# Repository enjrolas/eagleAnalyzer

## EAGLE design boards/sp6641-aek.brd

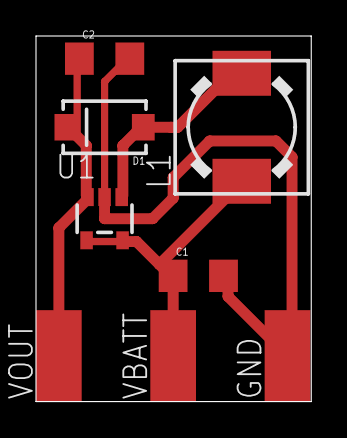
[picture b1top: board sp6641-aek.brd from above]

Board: 2 copper layers, 15.3 x 20.3 mm, 8 parts (0 on the bottom side), 4 nets.

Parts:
C1, C2: 22uF; 1206
D1: DIODE-SCHOTTKY_; SMA-DIODE
GND: SMD2,54-5,08
L1: 22uH; DR73
U1: SP6641AEK; SOT23-5
VBATT: SMD2,54-5,08
VOUT: SMD2,54-5,08

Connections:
GND: C1.2, C2.2, GND.1, U1.2
unnamed: D1.A, L1.2, U1.1
VBATT: C1.1, L1.1, U1.4, U1.5, VBATT.1
VOUT: C2.1, D1.C, U1.3, VOUT.1

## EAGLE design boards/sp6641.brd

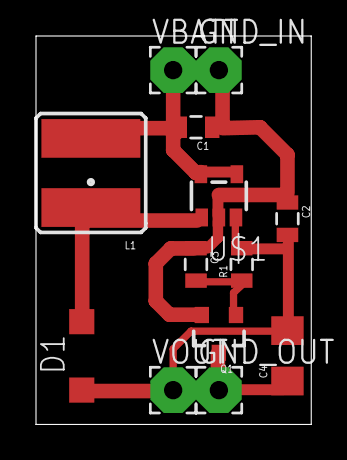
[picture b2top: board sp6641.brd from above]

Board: 2 copper layers, 15.3 x 21.6 mm, 13 parts (0 on the bottom side), 6 nets.

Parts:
C1, C2: 22uF; 0805
C3: 10nF; 0805
C4: 1uF; 1206
D1: MBR0520; SOD123
GND_IN: 2,54/1,0
GND_OUT: 2,54/1,0
L1: 22uH; CR54
Q1: SOT23-3
R1: 2M; 0805
U$1: SP6641A; SOT23-5
VBATT: 2,54/1,0
VOUT: 2,54/1,0

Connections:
GND: C1.1, C2.1, C3.1, GND_IN.1, Q1.2, U$1.2
GND_OUT: C4.1, GND_OUT.1, Q1.3
unnamed: C3.2, Q1.1, R1.1
unnamed: D1.A, L1.P$1, U$1.1
VBATT: C1.2, L1.P$2, U$1.4, U$1.5, VBATT.1
VOUT: C2.2, C4.2, D1.C, R1.2, U$1.3, VOUT.1

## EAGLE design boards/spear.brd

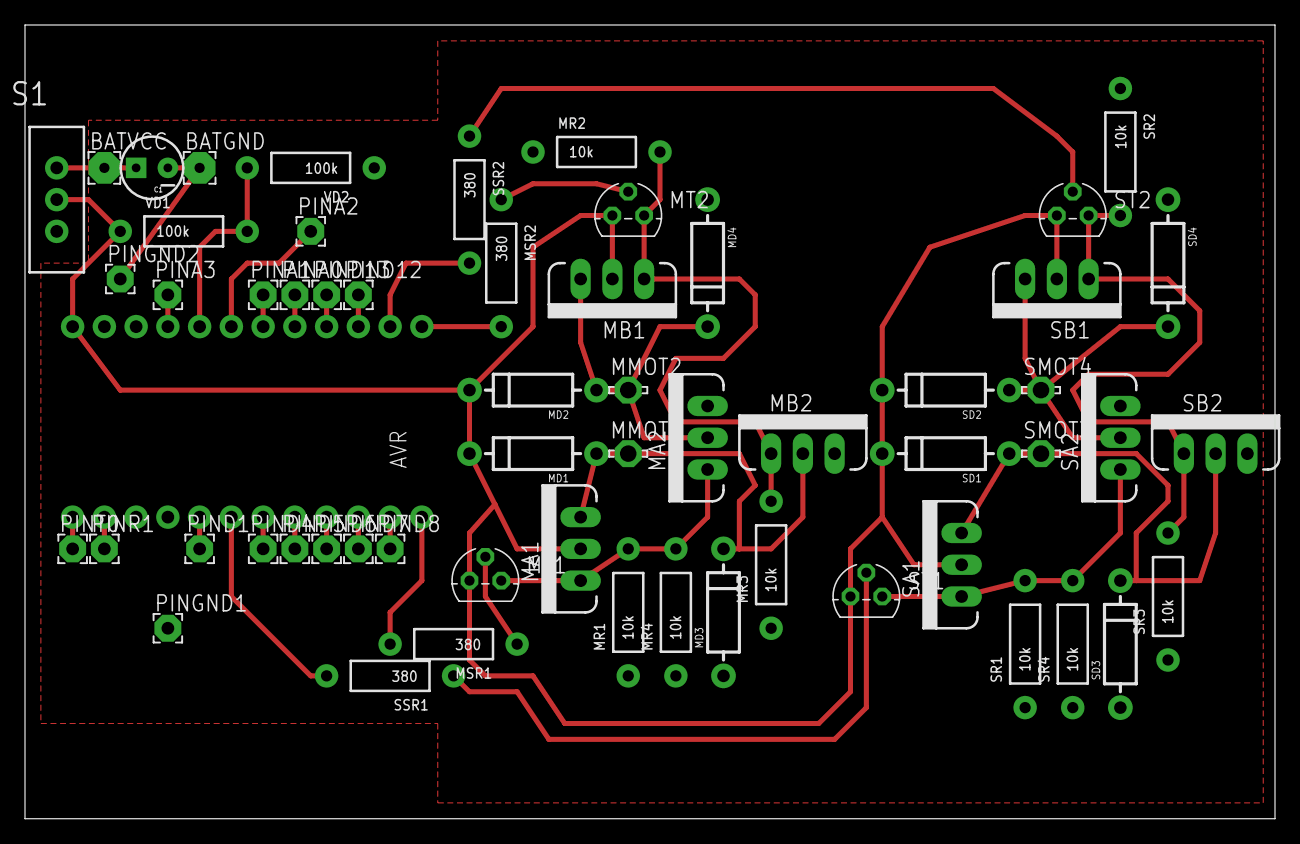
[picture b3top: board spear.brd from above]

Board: 2 copper layers, 100.0 x 63.5 mm, 59 parts (0 on the bottom side), 34 nets.

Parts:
AVR: ARDUINO_MINI
BATGND: WIREPAD2,54/0,8; 2,54/0,8
BATVCC: WIREPAD2,54/0,8; 2,54/0,8
C1: 10uf; CPOL-RADIAL-10UF-25V
MA1, MA2: MOSFET-NCHANNELFQP30N06L; TO220V
MB1, MB2: MOSFET-NCHANNELFQP30N06L; TO220V
MD1, MD2, MD3, MD4: DIODE-1N4001
MMOT1, MMOT2: LSP13
MR1, MR2, MR3, MR4: 10k; AXIAL-0.4
MSR1, MSR2: 380; AXIAL-0.4
MT1, MT2: 2N3904; TO92
PINA0, PINA1, PINA2, PINA3: WIREPAD2,15/1,0; 2,15/1,0
PIND1, PIND4, PIND5, PIND6, PIND7, PIND8, PIND12, PIND13: WIREPAD2,15/1,0; 2,15/1,0
PINGND1, PINGND2: WIREPAD2,15/1,0; 2,15/1,0
PINR1: WIREPAD2,15/1,0; 2,15/1,0
PINT0: WIREPAD2,15/1,0; 2,15/1,0
S1: SWITCH-SPDT
SA1, SA2: MOSFET-NCHANNELFQP30N06L; TO220V
SB1, SB2: MOSFET-NCHANNELFQP30N06L; TO220V
SD1, SD2, SD3, SD4: DIODE-1N4001
SMOT3, SMOT4: LSP13
SR1, SR2, SR3, SR4: 10k; AXIAL-0.4
SSR1, SSR2: 380; AXIAL-0.4
ST1, ST2: 2N3904; TO92
VD1, VD2: 100k; AXIAL-0.4

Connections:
GND: AVR.4, AVR.23, BATGND.1, C1.2, MA2.3, MB2.3, MD3.A, MD4.A, MR1.P$1, MR2.P$1, MR3.P$1, MR4.P$1, PINGND1.1, PINGND2.1, SA2.3, SB2.3, SD3.A, SD4.A, SR1.P$1, SR2.P$1, SR3.P$1, SR4.P$1, VD2.P$1
unnamed: AVR.13, MSR2.P$2
unnamed: AVR.12, MSR1.P$2
unnamed: AVR.6, SSR1.P$2
unnamed: AVR.14, SSR2.P$2
unnamed: MB1.1, MB2.1, MR2.P$2, MR3.P$2, MT2.1
unnamed: AVR.11, PIND8.1
unnamed: MSR1.P$1, MT1.2
unnamed: MSR2.P$1, MT2.2
unnamed: MA1.3, MB2.2, MD1.A, MD3.C, MMOT1.MP
unnamed: MA2.2, MB1.3, MD2.A, MD4.C, MMOT2.MP
unnamed: SA1.1, SA2.1, SR1.P$2, SR4.P$2, ST1.1
unnamed: MA1.1, MA2.1, MR1.P$2, MR4.P$2, MT1.1
unnamed: AVR.10, PIND7.1
unnamed: AVR.9, PIND6.1
unnamed: SB1.1, SB2.1, SR2.P$2, SR3.P$2, ST2.1
unnamed: AVR.8, PIND5.1
unnamed: AVR.7, PIND4.1
unnamed: AVR.15, PIND12.1
unnamed: AVR.16, PIND13.1
unnamed: SA2.2, SB1.3, SD2.A, SD4.C, SMOT4.MP
unnamed: AVR.17, PINA0.1
unnamed: SA1.3, SB2.2, SD1.A, SD3.C, SMOT3.MP
unnamed: AVR.18, PINA1.1
unnamed: AVR.19, PINA2.1
unnamed: AVR.21, PINA3.1
unnamed: BATVCC.1, C1.1, S1.1
unnamed: AVR.5, PIND1.1
unnamed: AVR.2, PINR1.1
unnamed: AVR.1, PINT0.1
PINVCC: AVR.20, VD1.P$2, VD2.P$2
SSIG1: SSR1.P$1, ST1.2
SSIG2: SSR2.P$1, ST2.2
VCC: AVR.24, MA1.2, MB1.2, MD1.C, MD2.C, MT1.3, MT2.3, S1.2, SA1.2, SB1.2, SD1.C, SD2.C, ST1.3, ST2.3, VD1.P$1

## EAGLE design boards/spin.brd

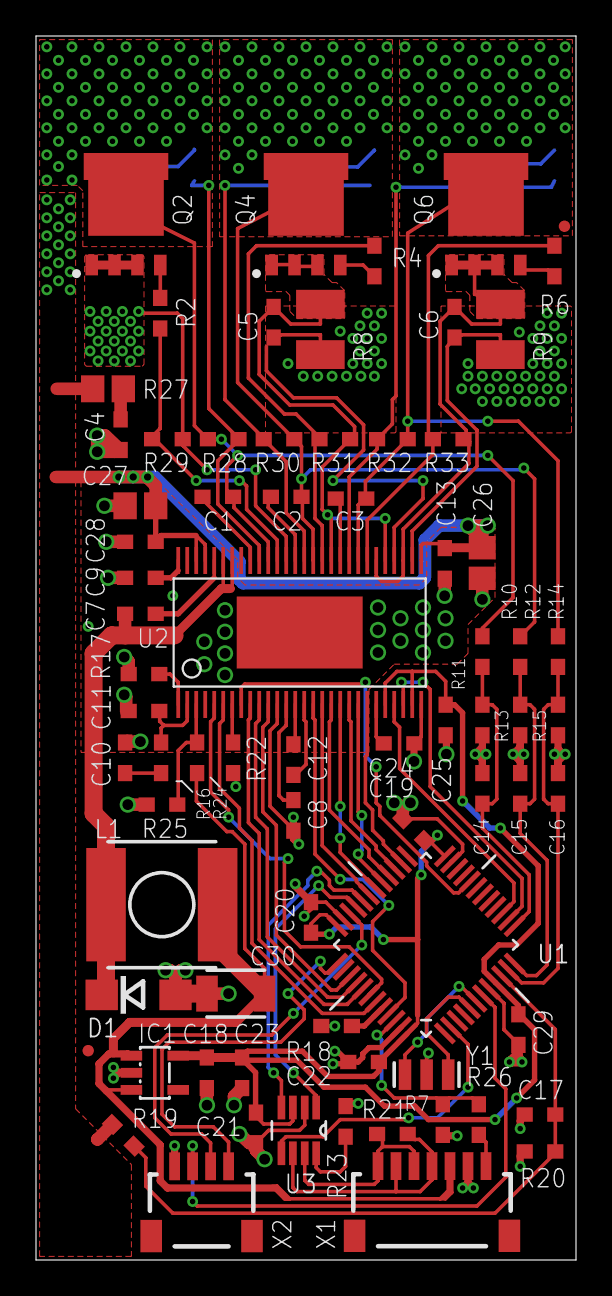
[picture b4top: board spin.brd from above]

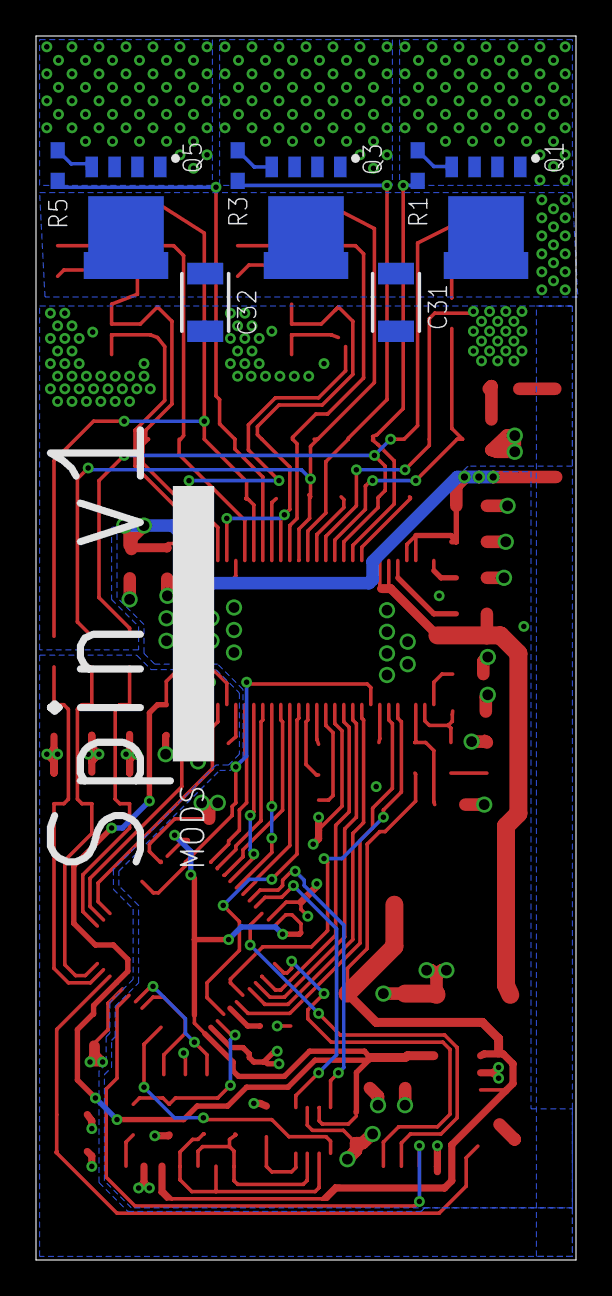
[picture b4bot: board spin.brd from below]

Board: 2 copper layers, 30.0 x 68.0 mm, 82 parts (8 on the bottom side), 72 nets.

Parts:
C1, C2, C3, C7, C13, C17, C19, C20, C21, C22, C23, C28: 100n; C0603
C4: 10n; C0603
C5, C6: 1n; C0603
C8, C18: 2u2; C0603
C9: 15n; C0603
C10: 6n8; C0603
C11: 120p; C0603
C12: 22n; C0603
C14, C15, C16: 2n2; C0603
C24, C25, C29: 1u; C0603
C26, C27: 4u7; C0805
C30: 47u; 1210
C31, C32: 10u; 1210
D1: STPS1H100AF; SMA
IC1: MCP1824MCP1824T-3302E/OT; SOT23-5L
JP1, JP2: FIDUCIALUFIDUCIAL; MICRO-FIDUCIAL
L1: 10u; NR6028
Q1, Q2, Q3, Q4, Q5, Q6: PSMN7R0-60YS; POWER-SO8-UNIVERSAL
R1, R2, R3, R4, R5, R6: 10R; R0603
R7: 2K2; R0603
R8, R9: R001; R1210
R10, R12, R14, R19: 56K; R0603
R11, R13, R15, R20: 3K9; R0603
R16, R18, R25: 10K; R0603
R17: 205K; R0603
R21: DNF; R0603
R22, R23: 0R; R0603
R24: 53K6; R0603
R26: 1K8; R0603
R27: 3R3; R0805
R28, R29, R30, R31, R32, R33: 100K; R0603
U1: STM32F103CBT6; QFP50P900X900X160-48N
U2: DRV8301DCA; TSSOP56P
U3: MAX3051EKA; SOT65P280X145-8N
X1: SM07B-SRSS-TB
X2: SM04B-SRSS-TB
Y1: RESONATORSMD; RESONATOR-SMD

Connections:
+3V3: C18.1, C19.1, C20.1, C21.1, C22.1, C23.1, C25.1, C29.1, IC1.5, U1.9, U1.24, U1.36, U1.48, U2.24, U2.27, U2.49, U3.3
+5V: C30.1, IC1.1, IC1.3, L1.2, R24.1, X1.5
A_HI: U1.31, U2.17
A_LO: U1.28, U2.18
B_HI: U1.30, U2.19
B_LO: U1.27, U2.20
CAN_H: R21.1, U3.7, X1.1, X1.3
CAN_L: R21.2, U3.6, X1.2, X1.4
CAN_RX: U1.32, U3.4
CAN_SHDN: U1.2, U3.5
CAN_TX: U1.33, U3.1
C_HI: U1.29, U2.21
C_LO: U1.26, U2.22
GND: C8.1, C9.2, C10.1, C11.1, C13.2, C18.2, C19.2, C20.2, C21.2, C22.2, C23.2, C26.2, C27.2, C28.2, C30.2, D1.A, IC1.2, R7.1, R17.2, R18.2, R22.2, R23.2, R25.1, U1.23, U1.35, U1.47, U2.12, U2.57, U3.2, X1.6, X2.1, Y1.2
GNDA: C14.2, C15.2, C16.2, C17.2, C24.1, C25.2, C29.2, R11.1, R13.1, R15.1, R20.1, U1.8, U2.28
I_B_SENSE: U1.15, U2.25
I_C_SENSE: U1.14, U2.26
unnamed: Q1.4, R1.2
unnamed: Q2.4, R2.2
unnamed: Q3.4, R3.2
unnamed: Q6.4, R6.2
unnamed: Q5.4, R5.2
unnamed: C3.2, Q5.1, Q5.2, Q5.3, Q6.5, Q6.6, R14.1, R32.1, U2.36
unnamed: C2.2, Q3.1, Q3.2, Q3.3, Q4.5, Q4.6, R12.1, R30.1, U2.41
unnamed: C1.2, Q1.1, Q1.2, Q1.3, Q2.5, Q2.6, R10.1, R28.1, U2.46
unnamed: R4.1, R31.2, U2.40
unnamed: R3.1, R30.2, U2.42
unnamed: R5.1, R32.2, U2.37
unnamed: R6.1, R33.2, U2.35
unnamed: R1.1, R28.2, U2.47
unnamed: C7.1, U2.52
unnamed: R2.1, R29.2, U2.45
unnamed: R26.2, X1.7
unnamed: C7.2, D1.C, L1.1, U2.50, U2.51
unnamed: C1.1, U2.48
unnamed: C2.1, U2.43
unnamed: C3.1, U2.38
unnamed: C11.2, R16.1, U2.2
unnamed: R17.1, U2.1
unnamed: R18.1, U1.44
unnamed: C8.2, U2.13
unnamed: R23.1, U3.8
unnamed: C12.2, U2.14
unnamed: C12.1, U2.15
unnamed: C10.2, R16.2
unnamed: C24.2, U2.23
unnamed: U1.39, U2.11
unnamed: C9.1, U2.56
unnamed: R22.1, U2.7
unnamed: R24.2, R25.2, U2.3
unnamed: U1.40, U2.10
unnamed: U1.41, U2.9
unnamed: U1.42, U2.5
unnamed: U1.43, U2.6
unnamed: U1.45, U2.16
unnamed: U1.6, Y1.1
unnamed: U1.5, Y1.3
unnamed: C4.1, R27.1
NRST: U1.7, X2.2
PGND: C4.2, C5.2, C6.2, C31.2, C32.2, Q2.1, Q2.2, Q2.3, R8.2, R9.2, R29.1, U2.30, U2.32, U2.44
PWM_IN: R7.2, R26.1, U1.46
PWR: C13.1, C26.1, C27.1, C28.1, C31.1, C32.1, Q1.5, Q1.6, Q3.5, Q3.6, Q5.5, Q5.6, R19.2, R27.2, U2.29, U2.53, U2.54
Q4: Q4.4, R4.2
SN1: C5.1, Q4.1, Q4.2, Q4.3, R8.1, R31.1, U2.33, U2.39
SN2: C6.1, Q6.1, Q6.2, Q6.3, R9.1, R33.1, U2.31, U2.34
SPI_!CS: U1.20, U2.8
SWDCLK: U1.37, X2.4
SWDIO: U1.34, X2.3
V_A_SENSE: C14.1, R10.2, R11.2, U1.13
V_BUS_SENSE: C17.1, R19.1, R20.2, U1.10
V_B_SENSE: C15.1, R12.2, R13.2, U1.12
V_C_SENSE: C16.1, R14.2, R15.2, U1.11

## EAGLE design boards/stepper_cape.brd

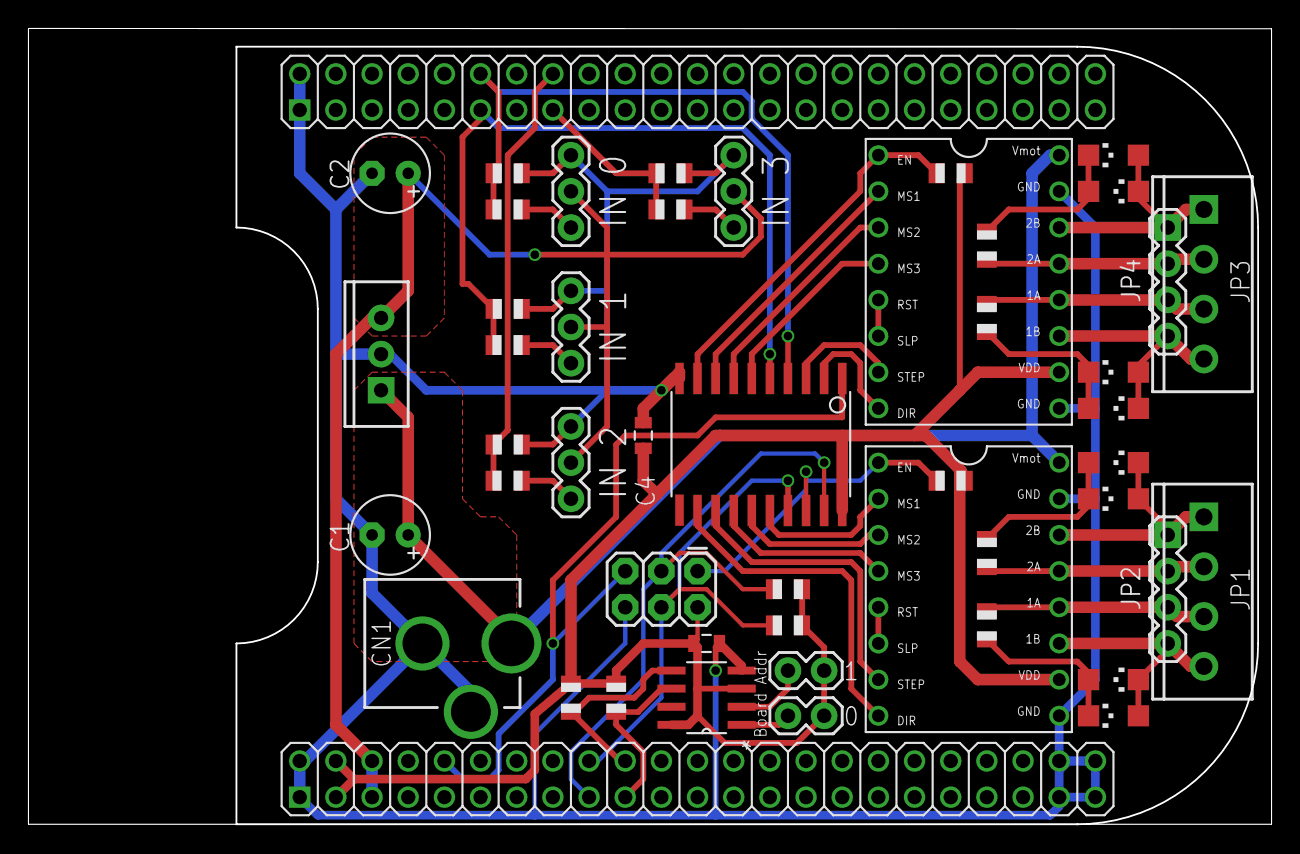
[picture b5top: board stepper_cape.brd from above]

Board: 2 copper layers, 87.3 x 55.9 mm, 49 parts (1 on the bottom side), 45 nets.

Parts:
C1, C2: 100u; E2,5-6
C3, C4: 0.1u; 0805
CN1: DCJACK_2MM_PTH
J1: ISP; 2X3
JP1, JP3: SCREWTERMINAL-3.5MM-4
JP2, JP4: 1X04
JP5, JP6, JP7, JP8: 1X03
JP9, JP10: 1X02
LED1, LED2, LED3, LED4, LED5, LED6, LED7, LED8: CHIPLED_1206
R1, R2, R3, R18: 5k6; R0805
R4, R5, R7, R8: 1k; R0805
R6, R9: 4k7; R0805
R10, R12, R14, R16: 10k; R0805
R11, R13, R15, R17: 20k; R0805
U1: CAT24C; SOIC127P600X175-8N
U2: LM7805; TO220-IGO
U$1: BEAGLEBONE_OUTLINE; BEAGLEBONE_SHIELD
U$2: ATTINY2313; SO20L$
U$3: OSHW_FILLX500_NOTEXT
X, X1: A4988BREAKOUT

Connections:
+3V3: C3.1, C4.1, J1.2, JP9.2, JP10.2, R1.2, R2.2, R3.2, R6.2, R9.2, R18.2, U1.3, U1.8, U$1.49, U$1.50, U$2.20, X.VDD, X1.VDD
+5V: C2.+, JP5.2, JP6.2, JP7.2, JP8.2, U2.OUT, U$1.51, U$1.52
GND: C1.-, C2.-, C3.2, C4.2, CN1.GND, CN1.GNDBREAK, J1.6, JP5.1, JP6.1, JP7.1, JP8.1, R11.1, R13.1, R15.1, R17.1, U1.4, U2.GND, U$1.1, U$1.2, U$1.47, U$1.48, U$1.89, U$1.90, U$1.91, U$1.92, U$2.10, X.GND, X.GND@0, X1.GND, X1.GND@0
I2C1_SCL: J1.3, R18.1, U$1.63, U$2.19
I2C1_SDA: J1.4, R1.1, U$1.64, U$2.17
I2C2_SCL: R2.1, U1.6, U$1.65
I2C2_SDA: R3.1, U1.5, U$1.66
IN_0: R12.1, R13.2, U$1.12, U$2.4
IN_1: R10.1, R11.2, U$1.11, U$2.5
IN_2: R14.1, R15.2, U$1.16
IN_3: R16.1, R17.2, U$1.15
MISO: J1.1, R6.1, U$2.18, X.EN
unnamed: JP9.1, U1.1
unnamed: U$2.2, X1.DIR
unnamed: JP10.1, U1.2
unnamed: U$2.3, X1.STEP
unnamed: JP1.1, JP2.1, LED1.C, LED2.A, X.2B
unnamed: U$2.6, X1.MS3
unnamed: U$2.7, X1.MS2
unnamed: U$2.8, X1.MS1
unnamed: X1.RST, X1.SLP
unnamed: JP3.1, JP4.1, LED5.C, LED6.A, X1.2B
unnamed: JP3.2, JP4.2, R4.2, X1.2A
unnamed: X.RST, X.SLP
unnamed: JP1.2, JP2.2, R7.2, X.2A
unnamed: JP1.3, JP2.3, R8.2, X.1A
unnamed: JP1.4, JP2.4, LED3.A, LED4.C, X.1B
unnamed: LED1.A, LED2.C, R7.1
unnamed: JP3.3, JP4.3, R5.2, X1.1A
unnamed: LED3.C, LED4.A, R8.1
unnamed: JP3.4, JP4.4, LED7.A, LED8.C, X1.1B
unnamed: LED5.A, LED6.C, R4.1
unnamed: LED7.C, LED8.A, R5.1
unnamed: R9.1, U$2.9, X1.EN
unnamed: U$2.12, X.DIR
unnamed: U$2.13, X.STEP
unnamed: JP6.3, R12.2
unnamed: JP5.3, R10.2
unnamed: JP7.3, R14.2
unnamed: JP8.3, R16.2
unnamed: U$2.14, X.MS3
unnamed: U$2.15, X.MS2
unnamed: U$2.16, X.MS1
RESET: J1.5, U$1.56, U$2.1
V+: C1.+, CN1.PWR, U2.IN, X.VMOT, X1.VMOT

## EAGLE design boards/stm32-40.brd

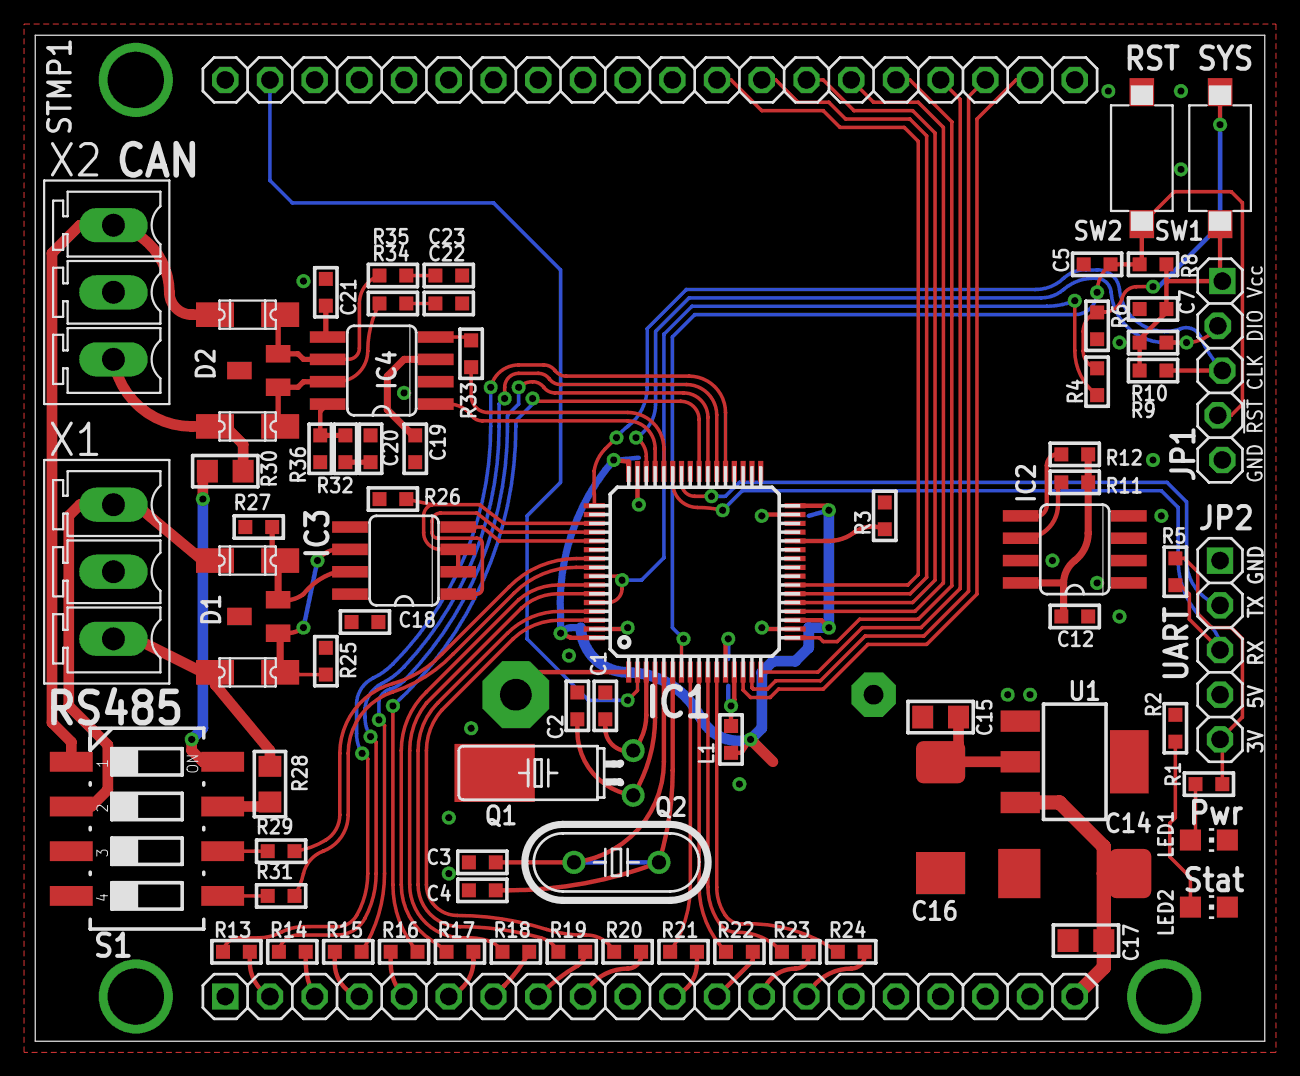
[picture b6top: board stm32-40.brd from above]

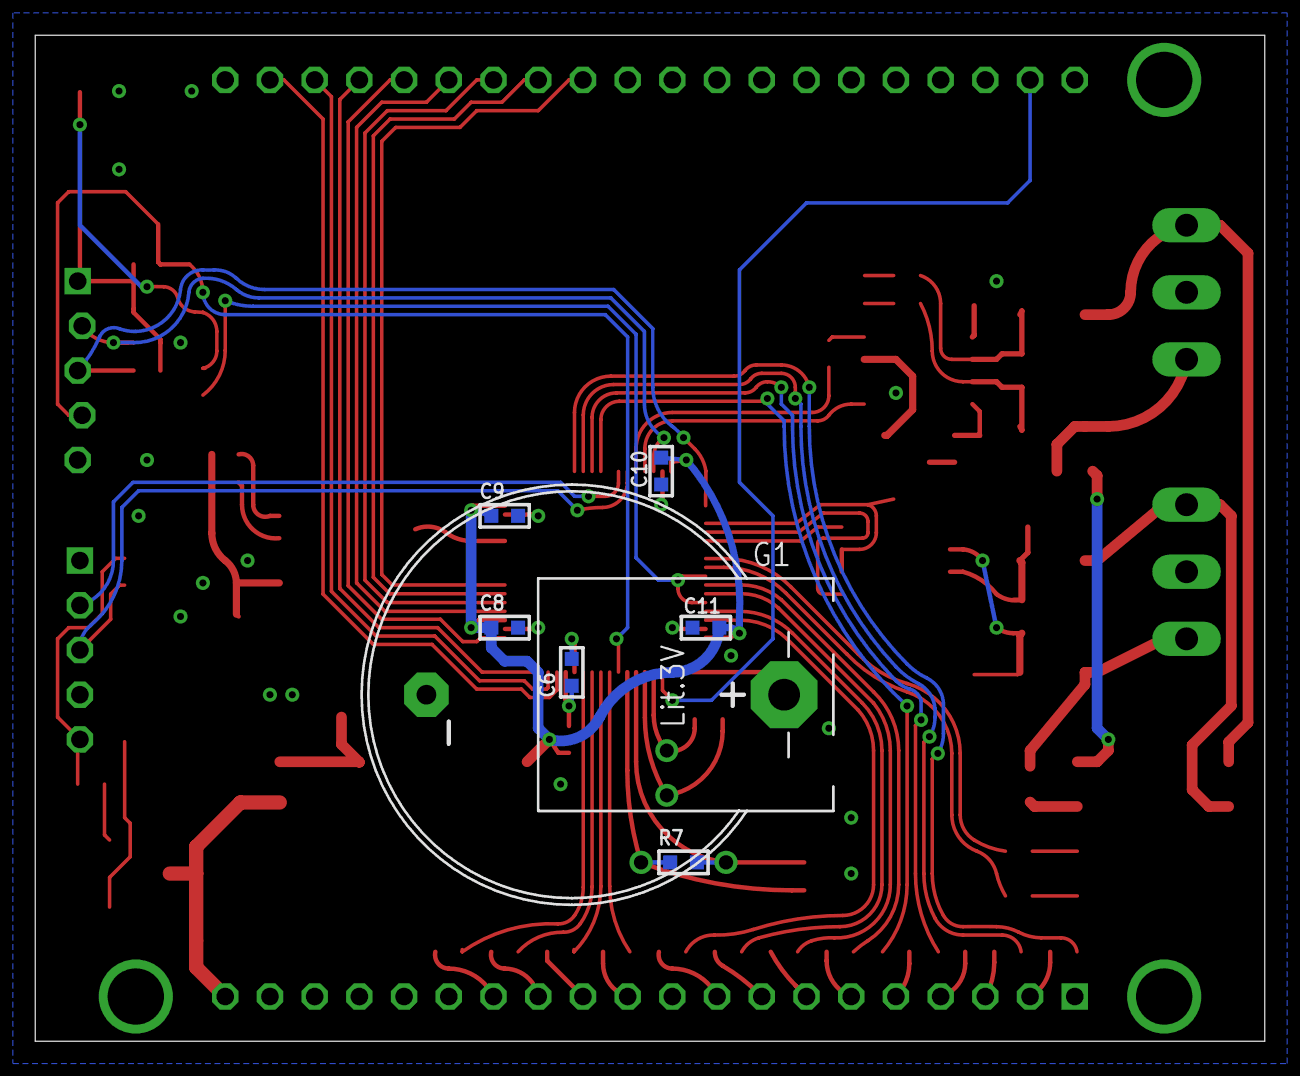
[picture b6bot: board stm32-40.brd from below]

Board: 2 copper layers, 69.8 x 57.1 mm, 83 parts (7 on the bottom side), 78 nets.

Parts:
C1, C2: 10pF; C0603
C3, C4: 22pF; C0603
C5, C6, C7, C8, C9, C10, C11, C12, C18, C19, C20, C21: 0.1; C0603
C14, C16: 100uF/6V3; SMC_D
C15, C17: 0.1; C0805
C22, C23: 560pF; C0603
D1, D2: PESD1CAN; SOT23
F1, F2, F3, F4: 0.2A; 1206L
G1: LITHOLDER
IC1: STM32F103RBT6; TQFP64
IC2: CAT24M01WI-GT3; SO08
IC3: MAX487-S; SO08
IC4: AMIS30663CANG2G; SO08
JP1: 1X05
JP2: UART_1X05
L1: bead; L0603
LED1, LED2: CHIP-LED0805
Q1: 32768Hz; TC38H-G
Q2: 8MHz; HC49/S
R1, R2: 220; R0603
R3, R4, R5, R8, R9, R10, R26: 10K; R0603
R6: 2.2K; R0603
R7: 1M; R0603
R11, R12: 4.7K; R0603
R13, R14, R15, R16, R17, R18, R19, R20, R21, R22, R23, R24: 10; R0603
R25, R27: 560; R0603
R28, R30: 120; R0805
R29, R31: 330; R0603
R32: 0; R0603
R33, R34, R35: 100; R0603
R36: NC; R0603
S1: 219-04; CTS-219-04
STMP1: STAMP-40
SW1, SW2: KSS-2EG4430
U1: SOT223
X1, X2: MCV3

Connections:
!RESET: C5.1, IC1.7, JP1.4, R8.1, SW2.2
+3V3: C7.1, C8.1, C9.1, C10.1, C11.1, C12.1, C15.1, C16.+, C20.1, IC1.19, IC1.32, IC1.48, IC1.64, IC2.8, JP1.1, JP2.5, L1.1, R1.1, R5.2, R8.2, R9.2, R10.2, R11.2, R12.2, R32.1, SW1.2, U1.2
+5V: C14.+, C17.1, C18.1, C19.1, IC3.8, IC4.3, JP2.4, R25.2, STMP1.20, U1.3
BOOT0: IC1.57, IC1.60, R4.1
BOOT1: IC1.28, R2.1, R3.1
CAN_CTRL: IC4.8, R32.2, R36.2
CAN_H: F3.P$2, R30.1, X2.1
CAN_L: F4.P$2, S1.1, X2.3
CAN_RX: IC1.44, R33.1
CAN_TX: IC1.45, IC4.1
DE3: IC1.53, IC3.4
GND: C1.2, C2.2, C3.2, C4.2, C5.2, C6.2, C7.2, C8.2, C9.2, C10.2, C11.2, C12.2, C14.-, C15.2, C16.-, C17.2, C18.2, C19.2, C20.2, C21.2, C22.2, C23.2, D1.3, D2.3, G1.-, IC1.12, IC1.18, IC1.31, IC1.47, IC1.63, IC2.1, IC2.2, IC2.3, IC2.4, IC2.7, IC3.5, IC4.2, JP1.5, JP2.1, LED1.C, LED2.C, Q1.GND, R3.2, R6.1, R26.1, R27.1, R36.1, S1.3, S1.4, STMP1.1, STMP1.10, STMP1.19, STMP1.21, STMP1.40, SW2.1, U1.1, X1.2, X2.2
unnamed: C21.1, IC4.5
unnamed: R30.2, S1.8
unnamed: R4.2, R6.2, SW1.1
unnamed: D1.2, F1.P$1, IC3.7, R27.2
unnamed: IC4.4, R33.2
unnamed: R28.2, S1.7
unnamed: R29.1, S1.6
unnamed: R31.1, S1.5
unnamed: R21.1, STMP1.11
unnamed: LED1.A, R1.2
unnamed: R22.1, STMP1.12
unnamed: R13.1, STMP1.2
unnamed: R14.1, STMP1.3
unnamed: R15.1, STMP1.4
unnamed: R16.1, STMP1.5
unnamed: R17.1, STMP1.6
unnamed: R18.1, STMP1.7
unnamed: R19.1, STMP1.8
unnamed: R20.1, STMP1.9
unnamed: R23.1, STMP1.13
unnamed: R24.1, STMP1.14
unnamed: LED2.A, R2.2
unnamed: D1.1, F2.P$1, IC3.6, R25.1
unnamed: D2.1, F3.P$1, IC4.7, R34.2
unnamed: D2.2, F4.P$1, IC4.6, R35.2
unnamed: C23.1, R35.1
unnamed: C22.1, R34.1
OSC32_IN: C1.1, IC1.3, Q1.2
OSC32_OUT: C2.1, IC1.4, Q1.1
OSC_IN: C3.1, IC1.5, Q2.1, R7.2
OSC_OUT: C4.1, IC1.6, Q2.2, R7.1
PA0: IC1.14, STMP1.22
PA1: IC1.15, STMP1.23
PA2: IC1.16, STMP1.24
PA3: IC1.17, STMP1.25
PA4: IC1.20, STMP1.26
PA5: IC1.21, STMP1.27
PA6: IC1.22, STMP1.28
PA7: IC1.23, STMP1.29
PC0: IC1.8, R21.2
PC1: IC1.9, R22.2
PC2: IC1.10, R23.2
PC3: IC1.11, R24.2
PC13: IC1.2, STMP1.39
RS485_A: F2.P$2, R28.1, X1.1
RS485_B: F1.P$2, S1.2, X1.3
RXD1: IC1.43, JP2.3, R5.1
RXD3: IC1.52, IC3.1
SCL2: IC1.29, IC2.6, R11.1
SDA2: IC1.30, IC2.5, R12.1
SW3: IC1.55, R29.2
SW4: IC1.56, R31.2
SWCLK: IC1.49, JP1.3, R9.1
SWDIO: IC1.46, JP1.2, R10.1
TIM3_CH1: IC1.37, R13.2
TIM3_CH2: IC1.38, R14.2
TIM3_CH3: IC1.39, R15.2
TIM3_CH4: IC1.40, R16.2
TIM4_CH1: IC1.58, R17.2
TIM4_CH2: IC1.59, R18.2
TIM4_CH3: IC1.61, R19.2
TIM4_CH4: IC1.62, R20.2
TXD1: IC1.42, JP2.2
TXD3: IC1.51, IC3.2, IC3.3, R26.2
VBAT: G1.+, IC1.1
VDDA: C6.1, IC1.13, L1.2

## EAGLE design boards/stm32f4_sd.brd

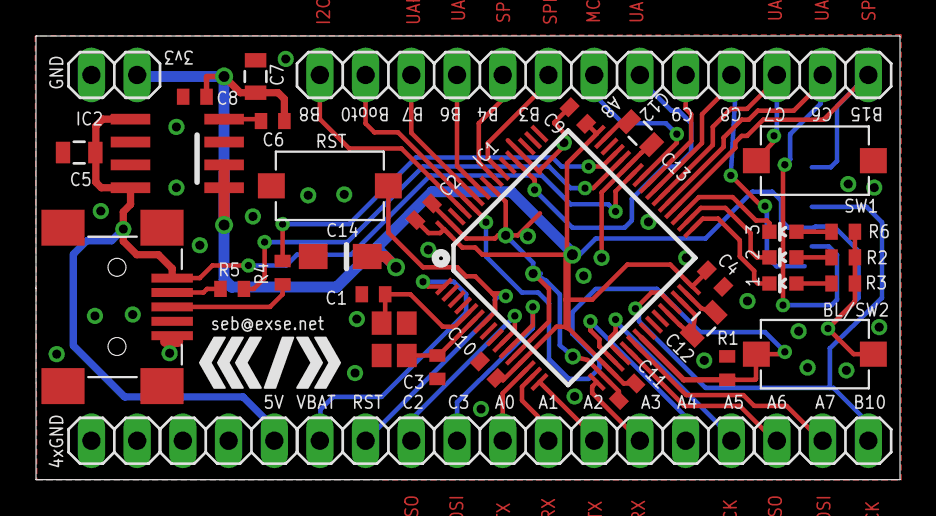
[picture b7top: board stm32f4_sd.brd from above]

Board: 2 copper layers, 48.0 x 24.6 mm, 38 parts (1 on the bottom side), 44 nets.

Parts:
BL/SW2: SWITCH_MCTAEF
C1, C3: 22pF; C0402
C2, C4, C9, C10, C11: 100nF; C0402
C5, C7: 1µF; 0805
C6, C8: 10nF; C0402
C12, C13: 2,2µF; 0805
C14: SMC_A
CN1: USB-MINIB
IC1: STM32F405RGT; LQFP64
IC2: LT1763CS8-3.3; SOIC8
JP1, JP2: 1X10
JP3, JP4: 1X02
JP5, JP6, JP7: 1X03
L1: 25Mhz; X22
LED1, LED2, LED3: LED-0603
R1: 10k; R0402
R2, R3, R4, R5, R6: 150R; R0402
RST: SWITCH_MCTAEF
SW1: SWITCH_MCTAEF
U1: 2908-05WB-MG; MICRO-SD-SOCKET-PP

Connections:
+3V3: BL/SW2.1, C2.2, C4.1, C6.2, C7.1, C8.2, C9.1, C10.2, C11.1, C14.+, IC1.13, IC1.19, IC1.32, IC1.48, IC1.64, IC2.1, IC2.2, JP3.2, R2.1, R3.2, R6.1, U1.4
+5V: C5.1, CN1.VBUS, IC1.42, IC2.5, IC2.8, JP7.1
A0: IC1.14, JP1.6
A1: IC1.15, JP1.5
A3: IC1.17, JP1.3
A4: IC1.20, JP1.2
A5: IC1.21, JP1.1
A6: IC1.22, JP5.3
A7: IC1.23, JP5.2
A8: IC1.41, JP2.7
B4: IC1.56, JP2.5
B6: IC1.58, JP2.4
B7: IC1.59, JP2.3
B8: IC1.61, JP2.1
B10: IC1.29, JP5.1, U1.5
B14: IC1.36, JP6.3, U1.7
B15: IC1.37, JP6.2, U1.3
BOOT: BL/SW2.2, IC1.24, IC1.60, JP2.2, R1.2
C2: IC1.10, JP1.8
C3: IC1.11, JP1.7
C6: IC1.38, JP6.1, SW1.1
C7: IC1.39, JP2.10, U1.2
C8: IC1.40, JP2.9
C12: IC1.53, JP2.8
GND: C1.1, C2.1, C3.1, C4.2, C5.2, C7.2, C8.1, C9.2, C10.1, C11.2, C12.2, C13.1, C14.-, CN1.GND, IC1.12, IC1.18, IC1.28, IC1.30, IC1.43, IC1.52, IC1.57, IC1.63, IC2.3, IC2.6, IC2.7, JP3.1, JP4.1, JP4.2, JP7.2, JP7.3, R1.1, RST.1, SW1.2, U1.6, U1.CD1, U1.CD2, U1.GND1, U1.GND3
unnamed: IC1.35, LED3.C
unnamed: IC1.16, JP1.4
unnamed: C3.2, IC1.6, L1.1
unnamed: C1.2, IC1.5, L1.3
unnamed: IC1.7, JP1.9, RST.2
unnamed: LED3.A, R6.2
unnamed: IC1.44, R5.2
unnamed: C12.1, IC1.31
unnamed: C6.1, IC2.4
unnamed: C13.2, IC1.47
unnamed: IC1.33, LED2.C
unnamed: LED1.A, R2.2
unnamed: LED2.A, R3.1
unnamed: IC1.34, LED1.C
unnamed: IC1.45, R4.2
unnamed: CN1.D+, R4.1
unnamed: CN1.D-, R5.1
PB3: IC1.55, JP2.6
VBAT: IC1.1, JP1.10

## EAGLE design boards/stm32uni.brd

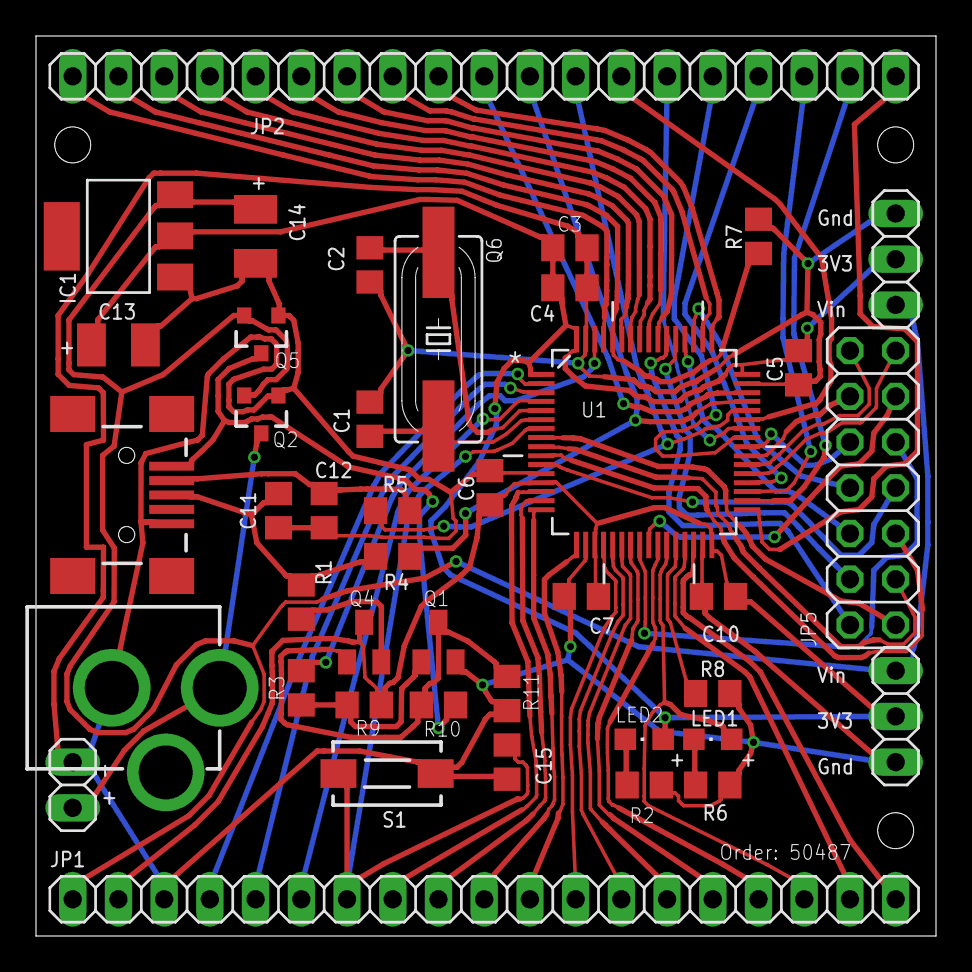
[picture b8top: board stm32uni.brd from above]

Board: 2 copper layers, 50.0 x 50.0 mm, 42 parts (0 on the bottom side), 65 nets.

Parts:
C1, C2, C15: C0805
C3: 4.7; C0805
C4, C5, C6, C7, C10: 0.1; C0805
C11, C12: 22nF; C0805
C13, C14: 10; SMC_B
IC1: LM1117; SOT223
J1: POWER_JACKPTH; POWER_JACK_PTH
JP1, JP2: 1X19
JP3, JP4: 1X03
JP5: 2X07
LED1, LED2: CHIPLED_0805
POWER: 1X02
Q1, Q4: SOT23
Q2, Q5: MOSFET-PCHANNELSMD; SOT23-3
Q6: SM49
R1: 1.5k; R0805
R2, R3, R6: 1k; R0805
R4, R5: 33; R0805
R7, R8, R10: 10k; R0805
R9: 47k; R0805
R11: 36k; R0805
S1: DTSM-3
U1: STM32F103RET6; QFP50P1200X1200X160-64N
U$1: USB-MINIB-5PIN; USB-MINIB

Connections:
+3V3: C3.1, C4.1, C5.1, C6.1, C7.1, C10.1, C13.+, IC1.2, JP1.2, JP3.2, JP4.2, LED2.A, Q4.3, R9.2, U1.1, U1.13, U1.19, U1.32, U1.48, U1.64
+5V: C14.+, IC1.3, JP1.1, JP3.1, JP4.1, Q2.2, Q5.2
BOOT0: JP2.2, R7.2, U1.60
GND: C1.2, C2.2, C3.2, C4.2, C5.2, C6.2, C7.2, C10.2, C11.2, C12.2, C13.-, C14.-, C15.2, IC1.1, J1.GND, JP1.3, JP3.3, JP4.3, POWER.2, Q1.2, Q2.1, Q5.1, R2.1, R6.1, R7.1, R8.1, R11.1, S1.1, U1.12, U1.18, U1.31, U1.47, U1.63, U$1.GND
unnamed: LED2.C, R2.2
unnamed: J1.PWR, POWER.1, Q2.3
unnamed: Q1.1, R3.2, R9.1
unnamed: Q1.3, Q4.1, R10.1, R11.2
unnamed: C11.1, R1.1, R4.1, U$1.D+
unnamed: C12.1, R5.1, U$1.D-
unnamed: JP5.1, U1.8
unnamed: Q4.2, R1.2
unnamed: JP5.3, U1.9
unnamed: JP5.5, U1.10
unnamed: JP5.7, U1.11
unnamed: JP5.9, U1.24
unnamed: JP5.11, U1.25
unnamed: JP5.13, U1.37
unnamed: JP5.14, U1.38
unnamed: JP5.12, U1.39
unnamed: JP5.10, U1.40
unnamed: JP5.8, U1.51
unnamed: JP5.6, U1.52
unnamed: JP5.4, U1.53
unnamed: JP5.2, U1.54
unnamed: LED1.C, R6.2
OSC_IN: C2.1, Q6.1, U1.5
OSC_OUT: C1.1, Q6.2, U1.6
PA0: JP1.8, U1.14
PA1: JP1.9, U1.15
PA2: JP1.10, U1.16
PA3: JP1.11, U1.17
PA4: JP1.12, U1.20
PA5: JP1.13, U1.21
PA6: JP1.14, U1.22
PA7: JP1.15, U1.23
PA8: JP2.15, U1.41
PA9: JP2.14, U1.42
PA10: JP2.13, U1.43
PA11: JP2.12, R5.2, U1.44
PA12: JP2.11, R4.2, U1.45
PA13: JP2.10, U1.46
PA14: JP2.9, U1.49
PA15: JP2.8, U1.50
PB0: JP1.16, U1.26
PB1: JP1.17, LED1.A, U1.27
PB2: R8.2, U1.28
PB3: JP2.7, U1.55
PB4: JP2.6, U1.56
PB5: JP2.5, U1.57
PB6: JP2.4, U1.58
PB7: JP2.3, U1.59
PB8: JP2.1, U1.61
PB9: R3.1, U1.62
PB10: JP1.18, U1.29
PB11: JP1.19, U1.30
PB12: JP2.19, U1.33
PB13: JP2.18, U1.34
PB14: JP2.17, U1.35
PB15: JP2.16, U1.36
PC13: JP1.4, U1.2
PC14: JP1.5, U1.3
PC15: JP1.6, U1.4
RESET: C15.1, JP1.7, S1.2, U1.7
VBUS: Q5.3, R10.2, U$1.VBUS

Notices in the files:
parts and their libraries:
SparkFun: Licensing: CC v3.0 Share-Alike You are welcome to use this library for commercial purposes.
vreg-linear: 2009 Draw by Ivan A-R. License CC-BY-SA 3.0
